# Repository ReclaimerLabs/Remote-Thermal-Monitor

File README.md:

# Introduction

This board is a remote thermocouple monitor. It is pretty much a direct implementation of [**App Note SBAA189**](http://www.ti.com/lit/an/sbaa189/sbaa189.pdf) from TI. It uses a TI ADS1118 to read the thermocouple and a Particle Photon to connect via WiFi to the Internet. 

The first intended use was to monitor furnances in a materials science laboratory, providing a way for researchers to check on the health of the furnance from home without having to physically go to the lab. 

# Getting Started

The fastest way to get started is to run the Particle app on your phone to claim the Photon, then flash the example app through the Web IDE. Detailed step-by-step instructions are located [**here**](https://www.reclaimerlabs.com/blog/2016/12/29/wifi-thermocouple-monitor). The example app updates the temperature to the SparkFun Data stream and the Particle cloud once every five minutes or so. 

You can find the firmware libraries on github for the [**ADS1118**](https://github.com/ReclaimerLabs/ReclaimerLabs_ADS1118) and for [**thermocouples**](https://github.com/ReclaimerLabs/ReclaimerLabs_Thermocouple). 

# Questions and Comments

If you have questions or comments, you can email me directly at jason@reclaimerlabs.com. 

# License

The MIT License (MIT)

Copyright 2017 Jason Cerundolo

Permission is hereby granted, free of charge, to any person obtaining a copy of this hardware, software, and associated documentation files (the "Product"), to deal in the Product without restriction, including without limitation the rights to use, copy, modify, merge, publish, distribute, sublicense, and/or sell copies of the Product, and to permit persons to whom the Product is furnished to do so, subject to the following conditions:

The above copyright notice and this permission notice shall be included in all copies or substantial portions of the Product.

THE PRODUCT IS PROVIDED "AS IS", WITHOUT WARRANTY OF ANY KIND, EXPRESS OR IMPLIED, INCLUDING BUT NOT LIMITED TO THE WARRANTIES OF MERCHANTABILITY, FITNESS FOR A PARTICULAR PURPOSE AND NONINFRINGEMENT. IN NO EVENT SHALL THE AUTHORS OR COPYRIGHT HOLDERS BE LIABLE FOR ANY CLAIM, DAMAGES OR OTHER LIABILITY, WHETHER IN AN ACTION OF CONTRACT, TORT OR OTHERWISE, ARISING FROM, OUT OF OR IN CONNECTION WITH THE PRODUCT OR THE USE OR OTHER DEALINGS IN THE PRODUCT.

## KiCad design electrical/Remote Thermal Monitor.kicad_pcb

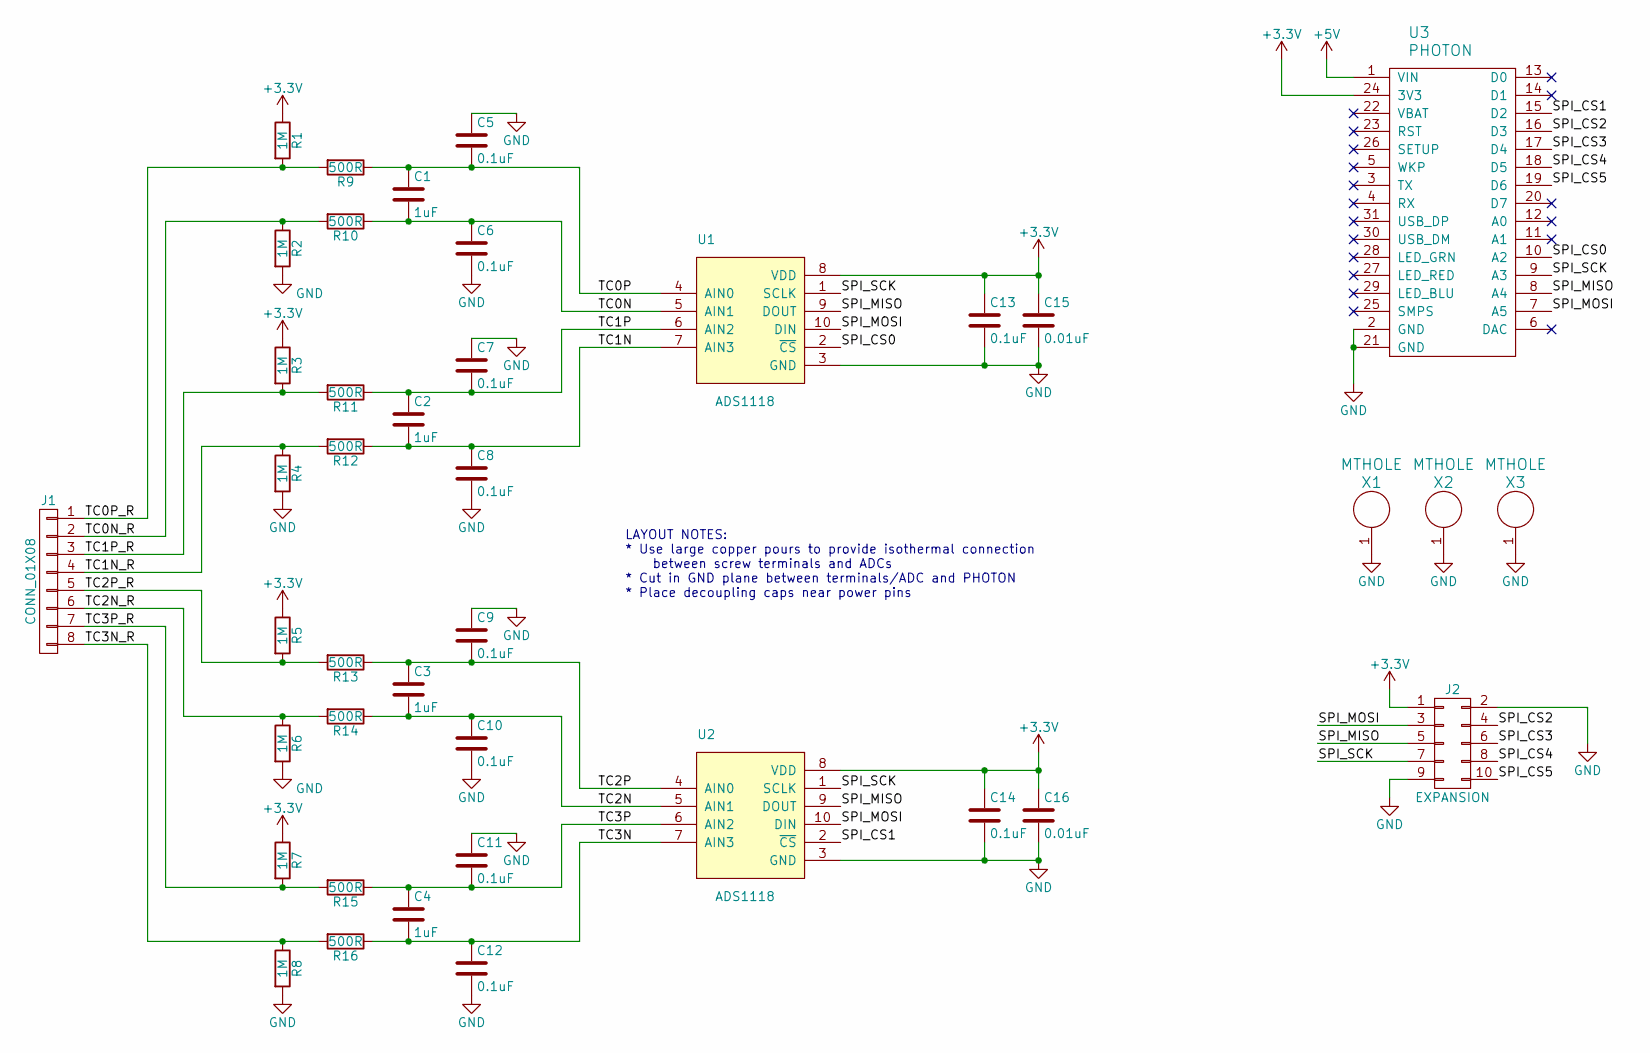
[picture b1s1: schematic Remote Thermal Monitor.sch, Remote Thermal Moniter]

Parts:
C1, C2, C3, C4: 1uF; C_0603
C5, C6, C7, C8, C9, C10, C11, C12, C13, C14: 0.1uF; C_0603
C15, C16: 0.01uF; C_0603
J1: CONN_01X08; TERM-BLOCK-3.5MM-8; Manufacturer Part Number OSTTE080104
J2: EXPANSION; HEADER_10_POL; Manufacturer Part Number 302-S101
R1, R2, R3, R4, R5, R6, R7, R8: 1M; C_0603
R9, R10, R11, R12, R13, R14, R15, R16: 500R; C_0603
U1, U2: ADS1118; VSSOP-10
U3: PHOTON
X1, X2, X3: MTHOLE; MountingHole_3.5mm_Pad_Via

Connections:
+3V3: C13.1, C14.1, C15.1, C16.1, J2.1, R1.1, R3.1, R5.1, R7.1, U1.8 (VDD), U2.8 (VDD), U3.24 (3V3)
+5V: U3.1 (VIN)
/SPI_CS0: U1.2 (~CS), U3.10 (A2)
/SPI_CS1: U2.2 (~CS), U3.15 (D2)
/SPI_CS2: J2.4, U3.16 (D3)
/SPI_CS3: J2.6, U3.17 (D4)
/SPI_CS4: J2.8, U3.18 (D5)
/SPI_CS5: J2.10, U3.19 (D6)
/SPI_MISO: J2.5, U1.9 (DOUT), U2.9 (DOUT), U3.8 (A4)
/SPI_MOSI: J2.3, U1.10 (DIN), U2.10 (DIN), U3.7 (A5)
/SPI_SCK: J2.7, U1.1 (SCLK), U2.1 (SCLK), U3.9 (A3)
/TC0N: C1.2, C6.1, R10.1, U1.5 (AIN1)
/TC0N_R: J1.2, R2.1, R10.2
/TC0P: C1.1, C5.2, R9.1, U1.4 (AIN0)
/TC0P_R: J1.1, R1.2, R9.2
/TC1N: C2.2, C8.1, R12.1, U1.7 (AIN3)
/TC1N_R: J1.4, R4.1, R12.2
/TC1P: C2.1, C7.2, R11.1, U1.6 (AIN2)
/TC1P_R: J1.3, R3.2, R11.2
/TC2N: C3.2, C10.1, R14.1, U2.5 (AIN1)
/TC2N_R: J1.6, R6.1, R14.2
/TC2P: C3.1, C9.2, R13.1, U2.4 (AIN0)
/TC2P_R: J1.5, R5.2, R13.2
/TC3N: C4.2, C12.1, R16.1, U2.7 (AIN3)
/TC3N_R: J1.8, R8.1, R16.2
/TC3P: C4.1, C11.2, R15.1, U2.6 (AIN2)
/TC3P_R: J1.7, R7.2, R15.2
GND: C5.1, C6.2, C7.1, C8.2, C9.1, C10.2, C11.1, C12.2, C13.2, C14.2, C15.2, C16.2, J2.2, J2.9, R2.2, R4.2, R6.2, R8.2, U1.3 (GND), U2.3 (GND), U3.2 (GND), U3.21 (GND), X1.1, X2.1, X3.1

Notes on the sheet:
LAYOUT NOTES: * Use large copper pours to provide isothermal connection between screw terminals and ADCs * Cut in GND plane between terminals/ADC and PHOTON * Place decoupling caps near power pins

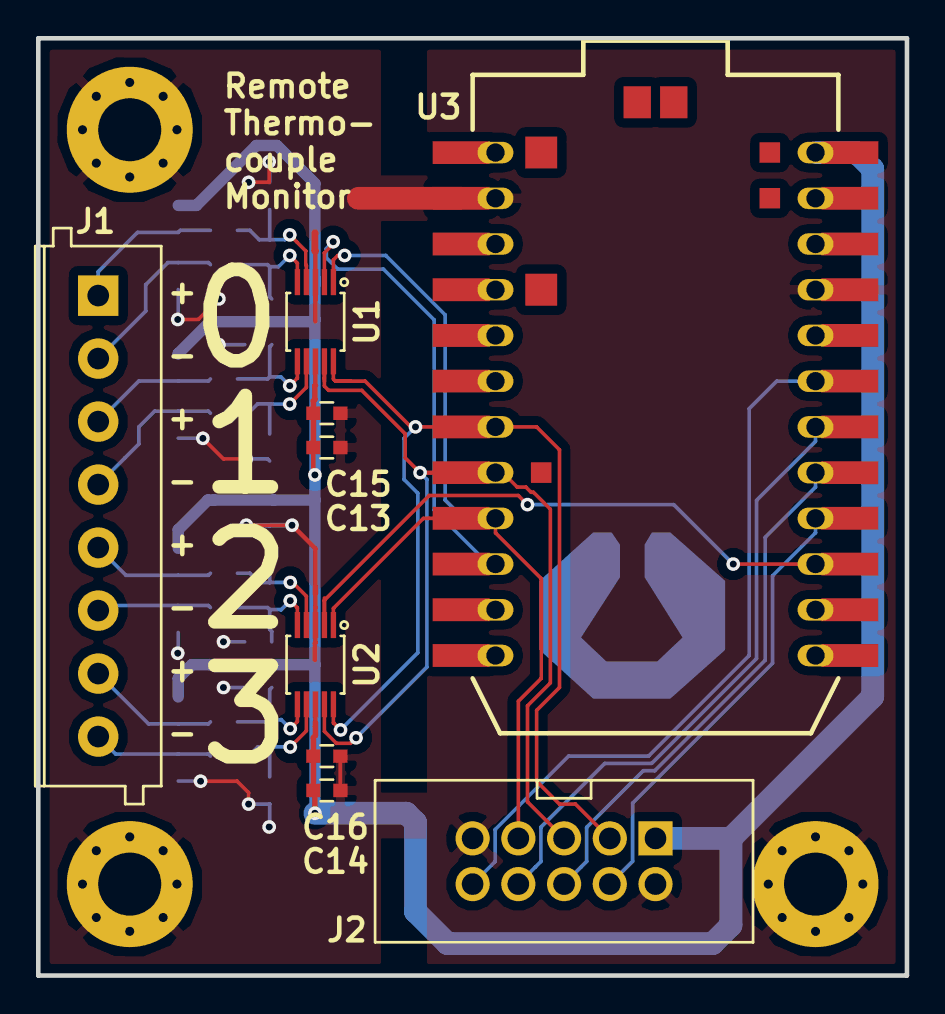
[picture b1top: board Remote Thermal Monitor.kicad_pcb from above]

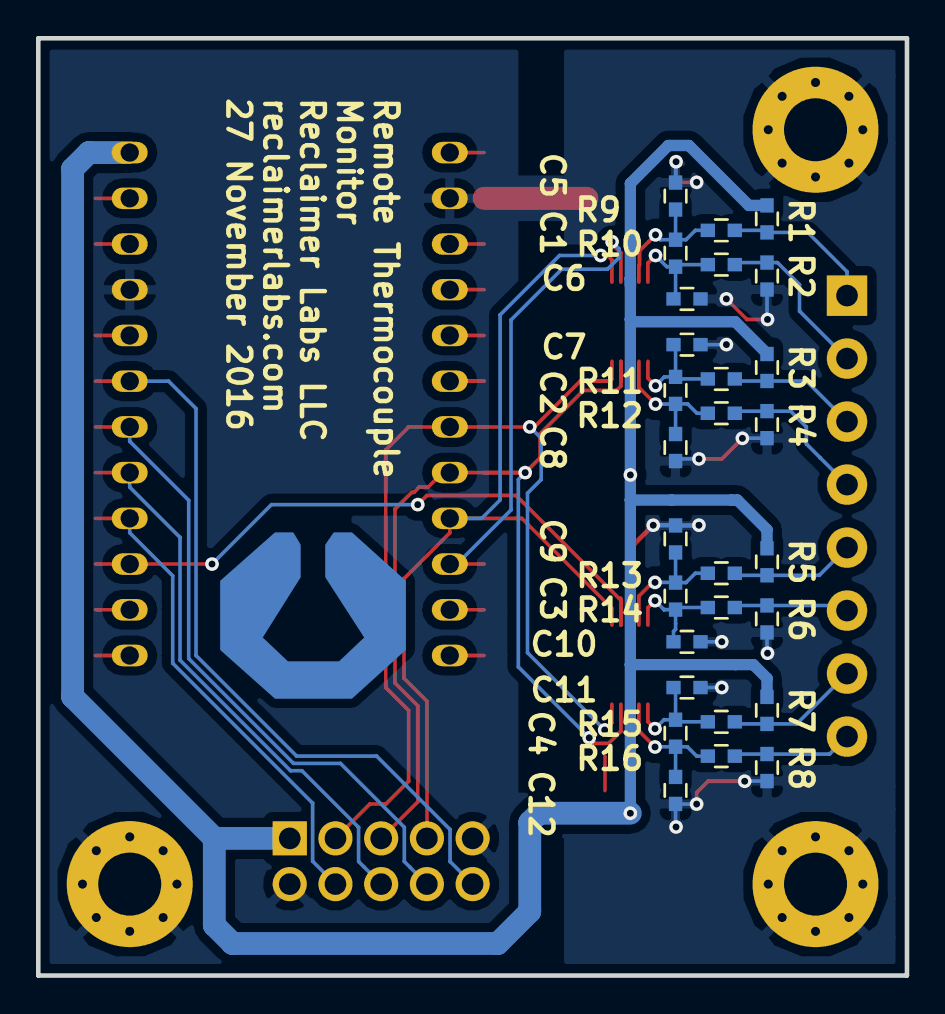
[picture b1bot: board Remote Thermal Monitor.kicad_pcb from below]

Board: 2 copper layers, 48.3 x 52.1 mm, 40 parts (28 on the bottom side), 27 nets.

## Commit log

2017-01-30 fixing formatting
